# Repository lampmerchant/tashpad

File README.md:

# TashPad

An adapter to make a Super Famicom/NES controller appear to an ADB Macintosh as a Gravis GamePad, targeting the PIC12F1501 (8 pins, ~$0.96) microcontroller.

## Technical Details

The firmware translates the buttons by position, not by color.  The Select and Start buttons emulate the toggle switch on the Gravis GamePad, with Select moving it toward the directional pad and Start moving it toward the buttons.  The SFC controller's L and R buttons duplicate the functionality of the Y and X buttons, respectively.

The ADB protocol used by the Gravis Mac GamePad is documented [here](https://github.com/lampmerchant/tashnotes/blob/main/macintosh/adb/protocols/gravis_mac_gamepad.md).  The protocol used by the SFC controller is documented [here](https://gamesx.com/controldata/snesdat.htm).

### Building Firmware

Building the firmware requires Microchip MPASM, which is included with their development environment, MPLAB. Note that you must use MPLAB X version 5.35 or earlier or MPLAB 8 as later versions of MPLAB X have removed MPASM.

The firmware can also be built using gpasm, an MPASM-compatible assembler that is part of the [gputils](https://gputils.sourceforge.io/) project.  Please note, however, that the release builds are built using MPASM and compatibility with gpasm is not tested.

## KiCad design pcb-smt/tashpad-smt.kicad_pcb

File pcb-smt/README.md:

# TashPad

This is a remix of the original tashpad PCB design. The changes in this version are:

- The through-hole capacitors, resistors, diodes, and PTC fuse have been replaced with SMT parts
- The PIC12F1501 has been changed from a DIP to a SOIC package
- An ICSP connector has been added for easily writing firmware to the PIC

The component sizes and spacing have been chosen to allow relatively easy hand assembly for anyone comfortable with SMT soldering. Most of the components are only there for RF and short protection (inspired from both old Macs and the SNES itself)

This folder (pcb-smt) contains the source KiCad files for the SMT remix version of the main board. Please check the Panels subfolder of the main pcb folder for the FR-4 front and back plates. Don't forget to order these at the same time as the main board!

## BOM
### Mandatory
Here is the BOM for the main board. Part numbers are what was tested on prototype boards but there are many alternatives that can also work

| Reference(s)          | Value      | Quantity | Notes                                    | Part number               |
|-----------------------|------------|----------|------------------------------------------|---------------------------|
| C1                    | 100nF      | 1        | ceramic capacitor 0805 (2012 Metric)     | Samsung CL21B104KBCNFNC   |
| C2, C3, C4            | 330pF      | 3        | ceramic capacitor 0805 (2012 Metric)     | Samsung CL21B331KBANNNC   |
| D1                    | Green      | 1        | 5mm any color 20 mA LED                  | Kingbright L-53SGD        |
| D2 to D7              | 1N4148     | 6        | general purpose switching diode SOD-323F | Diotec 1N4148WS           |
| F1                    | 200mA Fuse | 1        | PPTC resettable fuse 1812 (4532 Metric)  | Yageo SMD1812B020TF-J     |
| J1, J2                | Connector  | 2        | Mini DIN-4 (S-Video / ADB)               | TE 5749181-1              |
| J3                    | Connector  | 1        | SNES Angled (90°) connector              | ??? right gray one        |
| R2, R3, R4            | 100Ω       | 3        | thick film resistor 0805 (2012 metric)   | KOA Speer RK73H2ATTD1000F |
| R1                    | 330Ω       | 1        | thick film resistor 0805 (2012 metric)   | KOA Speer RK73H2ATTD3300F |
| R5                    | 10kΩ       | 1        | thick film resistor 0805 (2012 metric)   | KOA Speer RK73H2ATTD1002F |
| SW1                   | SPST       | 1        | right angle SPST switch                  | TE FSMRA4JH04             |
| U1                    | PIC        | 1        | 8-bit Microcontroller 8-SOIC PIC12F1501  | Microchip PIC12F1501-I/SN |
| J4                    | ICSP       | 1        | ICSP Connector (pin header)              | Adam Tech PH1-06-UA       |
| Case                  | ABS        | 1        | Instrument Case, ABS 2.6x2.6"            | HM 1593K(TBU\|GY\|BK)     |
| PCB Screws            | #4         | 4        | Phillips Pan Head screws #4 x 1/4"       | SERPAC 6004               |

### Optional

| Reference(s)          | Value      | Quantity | Notes                                    | Part number               |
|-----------------------|------------|----------|------------------------------------------|---------------------------|
| RF1                   | 1:1:1:1    | 1        | common mode chokes / filters             | HALO LD11-0246FLF         |
| R1                    | 2.87kΩ     | 1        | thick film resistor 0805 (2012 metric)   | KOA Speer RK73H2ATTD2871F |
| D1                    | Amber      | 1        | High efficiency 4000-8000mcd 5mm LED     | Cree C503B-ABN-CW0Z0251   |

:information_source: The common choke is recommended but pricey (about $5). When building without one, you need to bridge the holes with wires as shown on the PCB

R1 + D1 combo replaces the 300Ω + 20mA LED combo with a high efficiency LED which will be run with only 1mA. This puts less load on the ADB bus and is the recommended choice

### BOM (external links)
Here is a complete DigiKey cart (except the SNES connector).
- https://www.digikey.com/short/2qfqpwfb
Note that quantities in this cart are for 5 PCBAs, and it uses the optional high-efficiency LED and resistor combo. DigiKey does not stock the HALO common mode choke, and there is no known substitute.

## PCBs
The PCBs are simple 2-layer boards. The gerbers are available in the release section.
Check for the following files:
* TashPad_1.1.zip: main board revision 1.1
* TashPad_back_panel_1.1.zip: FR-4 back panel revision 1.1
* TashPad_front_panel_1.0.zip: FR-4 back panel revision 1.0

You should be able to use any mainstream PCB manufacturer for these. Nothing special about them. PCB thickness should be 1.6mm

On JLCPCB, select "Specify a location" to the option "Remove Order Number" for all of them

## Building
Building is straightforward. It's recommended to start with SMT components first, then through-hole components, beginning in the center of the board and working outward toward the edges.

:warning: Please note that you MUST solder the SNES connector with the front panel in position at the same time! Otherwise you will not be able to mount the front panel

As a test run, you can run TashPad without the PIC installed. ADB Passthrough should work, and you will be able to check that the PIC power rails are OK. This should avoid damaging the PIC or other stuff if something is wrong

Power pins location:

```
                  .--------.
             +5V -|01 \/ 08|- Ground
                 -|02    07|-
                 -|03    06|-
                 -|04    05|-
                  '--------'
```

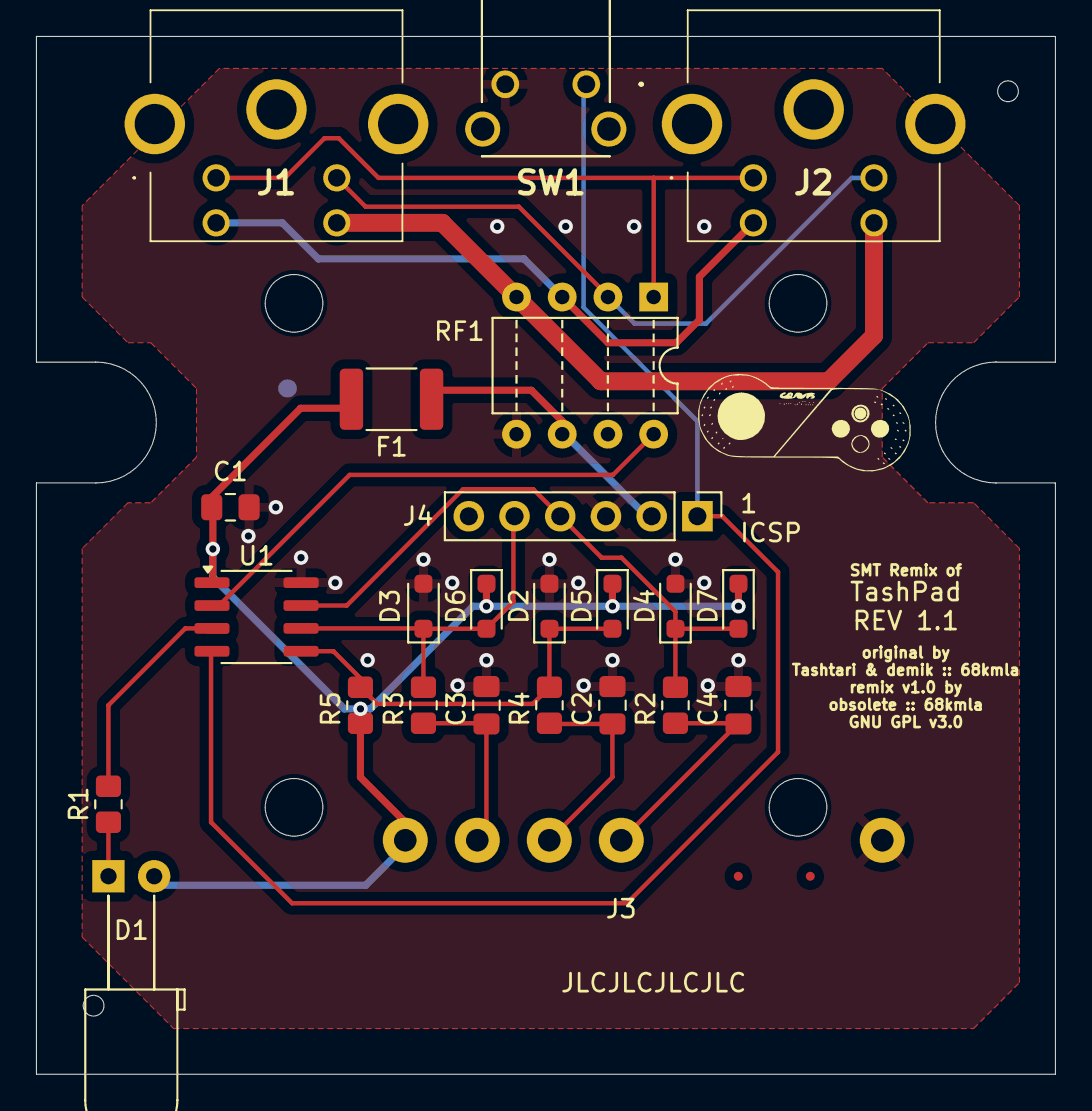
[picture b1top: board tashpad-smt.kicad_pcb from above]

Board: 2 copper layers, 56.6 x 57.7 mm, 30 parts (0 on the bottom side), 17 nets.

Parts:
C1: 100nF; C_0805_2012Metric_Pad1.18x1.45mm_HandSolder
C2, C3, C4: 330pF; C_0805_2012Metric_Pad1.18x1.45mm_HandSolder
D1: LED; LED_D5.0mm_Horizontal_O6.35mm_Z3.0mm
D2, D3, D4, D5, D6, D7: 1N4148; D_SOD-323_HandSoldering
F1: Polyfuse MF-R020; Fuse_1812_4532Metric_Pad1.30x3.40mm_HandSolder
H1, H2, H3, H4: M3; MountingHole_3.2mm_M3
H5, H6: 1.152mm; MountingHole_1.152mm
J1, J2: Mini-DIN-4; 57491811
J3: SNES Angled connector; SNES Controller
J4: ICSP; PinHeader_1x06_P2.54mm_Vertical
R1: 330Ω; R_0805_2012Metric_Pad1.20x1.40mm_HandSolder
R2, R3, R4: 100; R_0805_2012Metric_Pad1.20x1.40mm_HandSolder
R5: 10k; R_0805_2012Metric_Pad1.20x1.40mm_HandSolder
RF1: LD11-0246FLF; DIP-8_W7.62mm
SW1: 1-1825027-7; 118250277
U1: PIC12F1501-xP; SOIC-8_3.9x4.9mm_P1.27mm

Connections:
+5V: C1.2, D1.2 (A), D5.1 (K), D6.1 (K), D7.1 (K), F1.2, J3.1, R5.1, U1.1 (VDD)
+5V_PREFUSE: F1.1, J4.2, RF1.6
ADB: RF1.8, U1.2 (RA5)
GND: C1.1, C2.2, C3.2, C4.2, D2.2 (A), D3.2 (A), D4.2 (A), J3.7, J4.3, RF1.5, SW1.2 (B), U1.8 (VSS)
unnamed: D1.1 (K), R1.1
unnamed: D2.1 (K), D5.2 (A), R4.2, R5.2, U1.5 (RA2)
unnamed: D3.1 (K), D6.2 (A), J4.5, R3.2, U1.6 (RA1)
unnamed: D4.1 (K), D7.2 (A), J4.4, R2.2, U1.7 (RA0)
unnamed: C3.1, J3.2, R3.1
unnamed: C2.1, J3.3, R4.1
unnamed: C4.1, J3.4, R2.1
unnamed: J4.1, SW1.1 (A), U1.4 (RA3)
unnamed: J1.1, J2.1, RF1.1
unnamed: J1.2, J2.2, RF1.2
unnamed: J1.3, J2.3, RF1.3
unnamed: J1.4, J2.4, RF1.4
unnamed: R1.2, U1.3 (RA4)

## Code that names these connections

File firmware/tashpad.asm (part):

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PADHDLR	equ	0x34	;ADB handler ID when in gamepad mode

;Pin Assignments:
DAT_PIN	equ	RA0	;Data input pin
CLK_PIN	equ	RA1	;Data clock pin
LAT_PIN	equ	RA2	;Data latch pin
LED_PIN	equ	RA4	;LED pin
ADB_PIN	equ	RA5	;ADB pin

;FLAGS:
PADMODE	equ	7	;Set when device is in gamepad mode
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	btfss	INTCON,TMR0IE	; enabled, handle it as an event for the ADB
	bra	$+2		; state machine
	call	IntAdbTimer	; "
	movlb	7		;If the ADB pin has had a negative or positive
	btfsc	IOCAF,ADB_PIN	; edge, handle it as an event for the ADB state
	call	IntAdbEdge	; machine
	retfie

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	return
	
IntAdbEdge
	movlw	1 << ADB_PIN	;Toggle the edge that the IOC interrupt catches
	xorwf	IOCAN,F		; "
	xorwf	IOCAP,F		; "
	bcf	IOCAF,ADB_PIN	;Clear the interrupt flag
	btfsc	IOCAN,ADB_PIN	;If the edge we just caught is a rising edge,
	bra	IntAdbRising	; jump ahead, otherwise fall through
	;fall through

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	movwf	OSCCON

	banksel	IOCAN		;ADB sets IOCAF on negative edge
	movlw	(1 << ADB_PIN)
	movwf	IOCAN

	banksel	OPTION_REG	;Timer0 uses instruction clock, 1:16 prescaler,
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	banksel	ANSELA		;All pins digital, not analog
	clrf	ANSELA

	banksel	LATA		;Default state of output pins is low, ADB is
	clrf	LATA		; ready to be pulled low

	banksel	TRISA		;Latch, clock, and LED output, data input, ADB
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	retlw	low AdbFsaIdle	; "
AFSrq0	btfss	AP_FLAG,AP_SRQ	;If the user didn't call for a service request,
	retlw	low AdbFsaTlt	; just wait for Tlt to begin
	bcf	TRISA,ADB_PIN	;If the user did call for a service request,
	movlw	-63		; pull the pin low and set a timer for 252 us
	movlb	0		; above the 48 us we already waited to release
	movwf	TMR0		; it
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AdbFsaSrqEnd
	btfss	BSR,0		;On the off chance we're here because edge, go
	retlw	low AdbFsaSrqEnd; around again until the timer expires
	bsf	TRISA,ADB_PIN	;Release the pin that we pulled low to request
	retlw	low AdbFsaTlt	; service and wait for Tlt (could be right now)

AdbFsaTlt
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	clrf	TMR0		; to waiting for an attention pulse
	bcf	INTCON,TMR0IE	; "
	retlw	low AdbFsaIdle	; "
AFTxBD0	bcf	TRISA,ADB_PIN	;Pull the pin low
	lslf	AP_SR,F		;Shift the next bit to send into carry bit
	btfss	STATUS,Z	;If we shifted the placeholder out of the shift
	bra	AFTxBD1		; register, continue, else skip ahead
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AdbFsaTxBitU
	btfss	BSR,0		;If we're here because of the falling edge we
	retlw	low AdbFsaTxBitU; just triggered, ignore and return posthaste
	bsf	TRISA,ADB_PIN	;Release the pin
	DELAY	2		;Wait for it to actually go high
	movlb	0		;If the pin is still low, we've collided; set
	btfsc	PORTA,ADB_PIN	; the collision flag, clear the transmit flag,
	bra	AFTxBU0		; and go back to waiting for an attention pulse
	bsf	AP_FLAG,AP_COL	; "
	bcf	AP_FLAG,AP_TXI	; "
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	movwf	TMR0		; "
	bsf	INTCON,TMR0IE	; "
	movlb	7		;Reverse the IOC interrupt and clear the flag
	bcf	IOCAP,ADB_PIN	; set by releasing the pin so the timer we just
	bsf	IOCAN,ADB_PIN	; set doesn't immediately get reset
	bcf	IOCAF,ADB_PIN	; "
	retlw	low AdbFsaTxBitD;Timer will take us to the down phase again

AdbFsaTltEnd
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
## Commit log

2024-05-01 20240501
2024-05-31 20240531
2024-06-10 initial PCB release (main board + FR-4 panels)
2024-06-11 updated protocol link
2024-06-11 added ReadMe for BOM + Photo
2024-06-11 fixed PIC P/N
2024-06-12 PCB ReadMe updates
2024-06-14 Updated BOM + Mouser link
2026-05-30 mention gputils as potential build tool

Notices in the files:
pcb-smt/tashpad-smt.kicad_pcb:
GNU GPL v3.0
